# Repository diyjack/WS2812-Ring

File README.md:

# WS2812-Ring
Ring with 8/12/16/24/32/40/60 WS2812B intelligent RGB-LEDs.

## Shop
* [WS2812-Ring 8 (white)](http://www.watterott.com/en/WS2812B-RGB-Ring-8), [WS2812-Ring 8 (black)](http://www.watterott.com/en/WS2812-RGB-Ring-8-Black-Edition)
* [WS2812-Ring 12 (white)](http://www.watterott.com/en/WS2812B-RGB-Ring-12), [WS2812-Ring 12 (black)](http://www.watterott.com/en/WS2812-RGB-Ring-12-Black-Edition)
* [WS2812-Ring 16 (white)](http://www.watterott.com/en/WS2812B-RGB-Ring-16), [WS2812-Ring 16 (black)](http://www.watterott.com/en/WS2812-RGB-Ring-16-Black-Edition)
* [WS2812-Ring 24 (white)](http://www.watterott.com/en/WS2812B-RGB-Ring-24), [WS2812-Ring 24 (black)](http://www.watterott.com/en/WS2812-RGB-Ring-24-Black-Edition)
* [WS2812-Ring 32 (white)](http://www.watterott.com/en/WS2812B-RGB-Ring-32), [WS2812-Ring 32 (black)](http://www.watterott.com/en/WS2812-RGB-Ring-32-Black-Edition)
* [WS2812-Ring 40 (white)](http://www.watterott.com/en/WS2812B-RGB-Ring-40), [WS2812-Ring 40 (black)](http://www.watterott.com/en/WS2812-RGB-Ring-40-Black-Edition)
* [WS2812-Ring 60 (white)](http://www.watterott.com/en/WS2812B-RGB-Ring-60), [WS2812-Ring 60 (black)](http://www.watterott.com/en/WS2812-RGB-Ring-60-Black-Edition)
* [WS2812-Ring Set (white)](http://www.watterott.com/en/WS2812B-RGB-Ring-Set), [WS2812-Ring Set (black)](http://www.watterott.com/en/WS2812-RGB-Ring-Set-Black-Edition)

## Features
* WS2812 RGB-LED with built-in controller with serial interface
* 3 pin connection: VCC, GND, Data
* Controllable with Adafruit NeoPixel Library

## Hardware
* [Schematics + Layout](https://github.com/watterott/WS2812-Ring/tree/master/pcb)
* Datasheet: [WS2812B](https://github.com/watterott/WS2812-Breakout/raw/master/pcb/WS2812B.pdf)
* Note: for protection connect a >= 300 ohm resistor between the LED data input and controller output pin.

## Software
* [Light weight WS2811/WS2812 Library](https://github.com/cpldcpu/light_ws2812)
* [Adafruit NeoPixel Library](https://github.com/adafruit/Adafruit_NeoPixel)

## Videos
* [WS2812-Rings controlled by an Arduino](http://www.youtube.com/watch?v=nubyADJ7BFQ)
* [WS2812-Rings controlled by an Arduino](http://www.youtube.com/watch?v=e86KrhKNgWE)

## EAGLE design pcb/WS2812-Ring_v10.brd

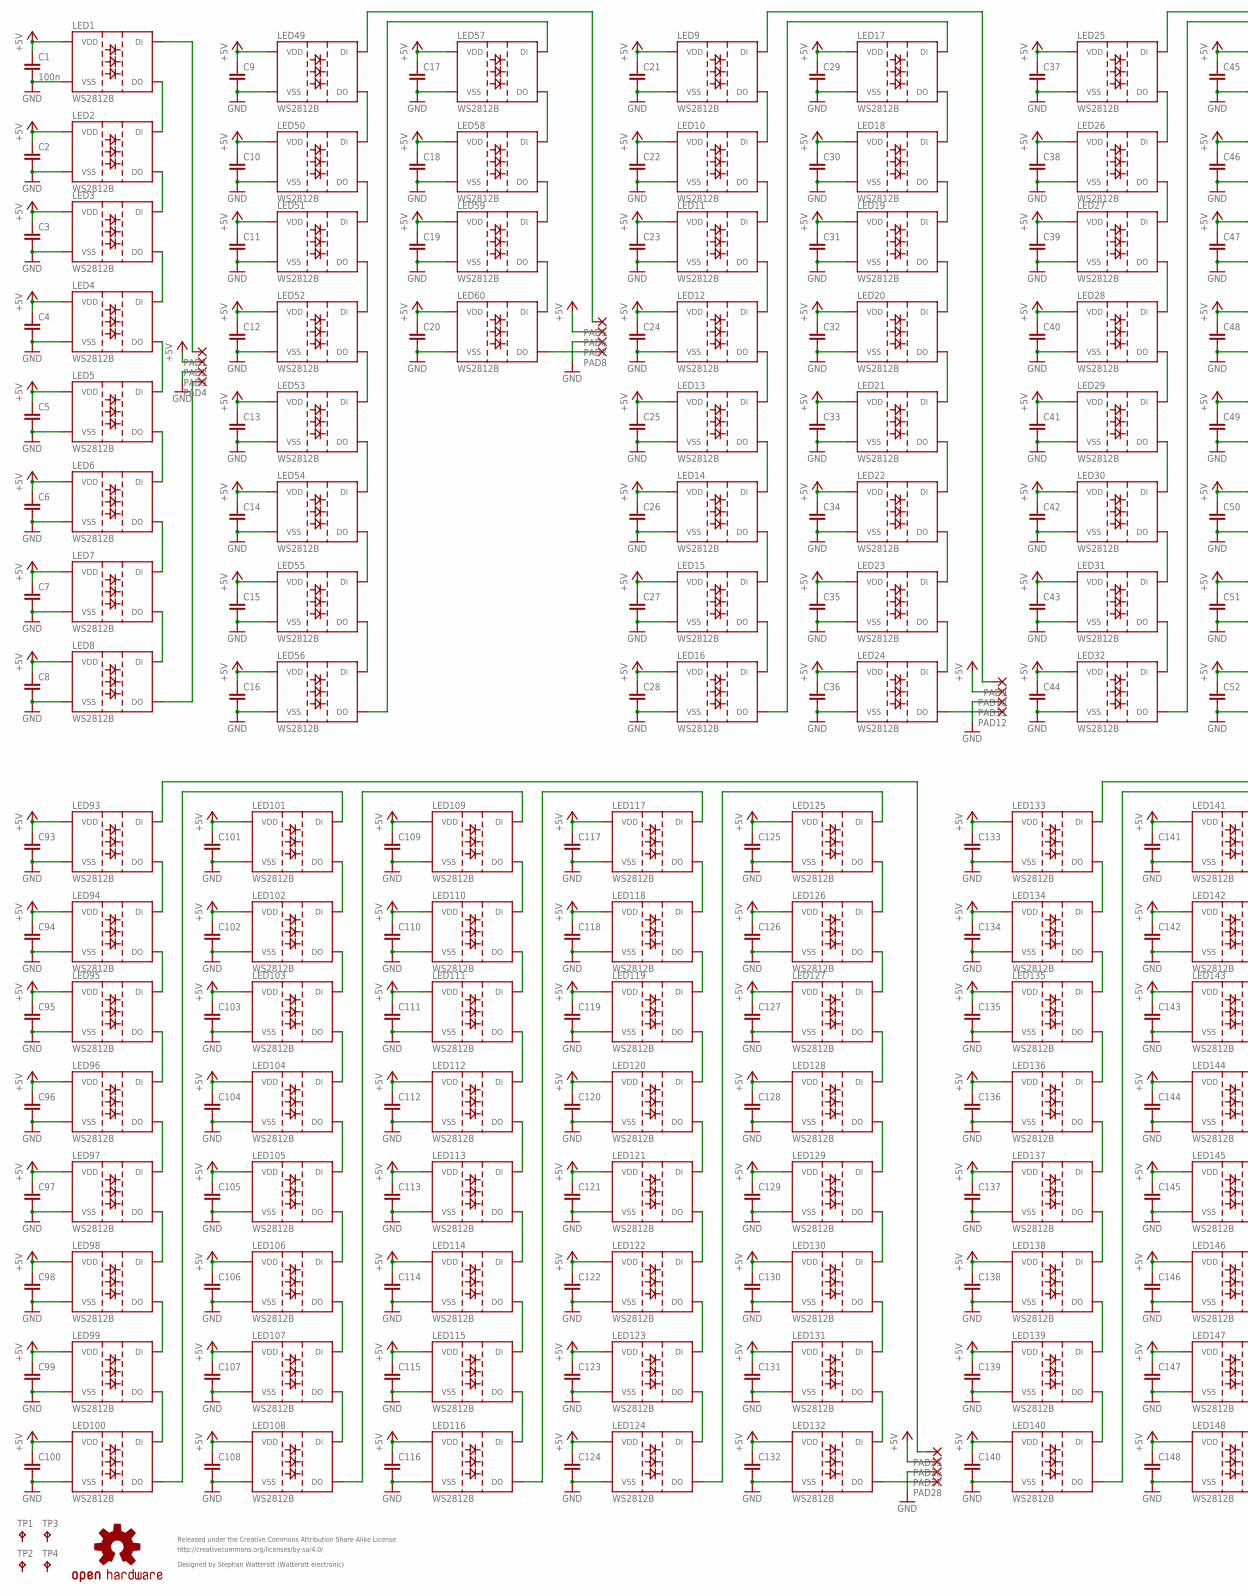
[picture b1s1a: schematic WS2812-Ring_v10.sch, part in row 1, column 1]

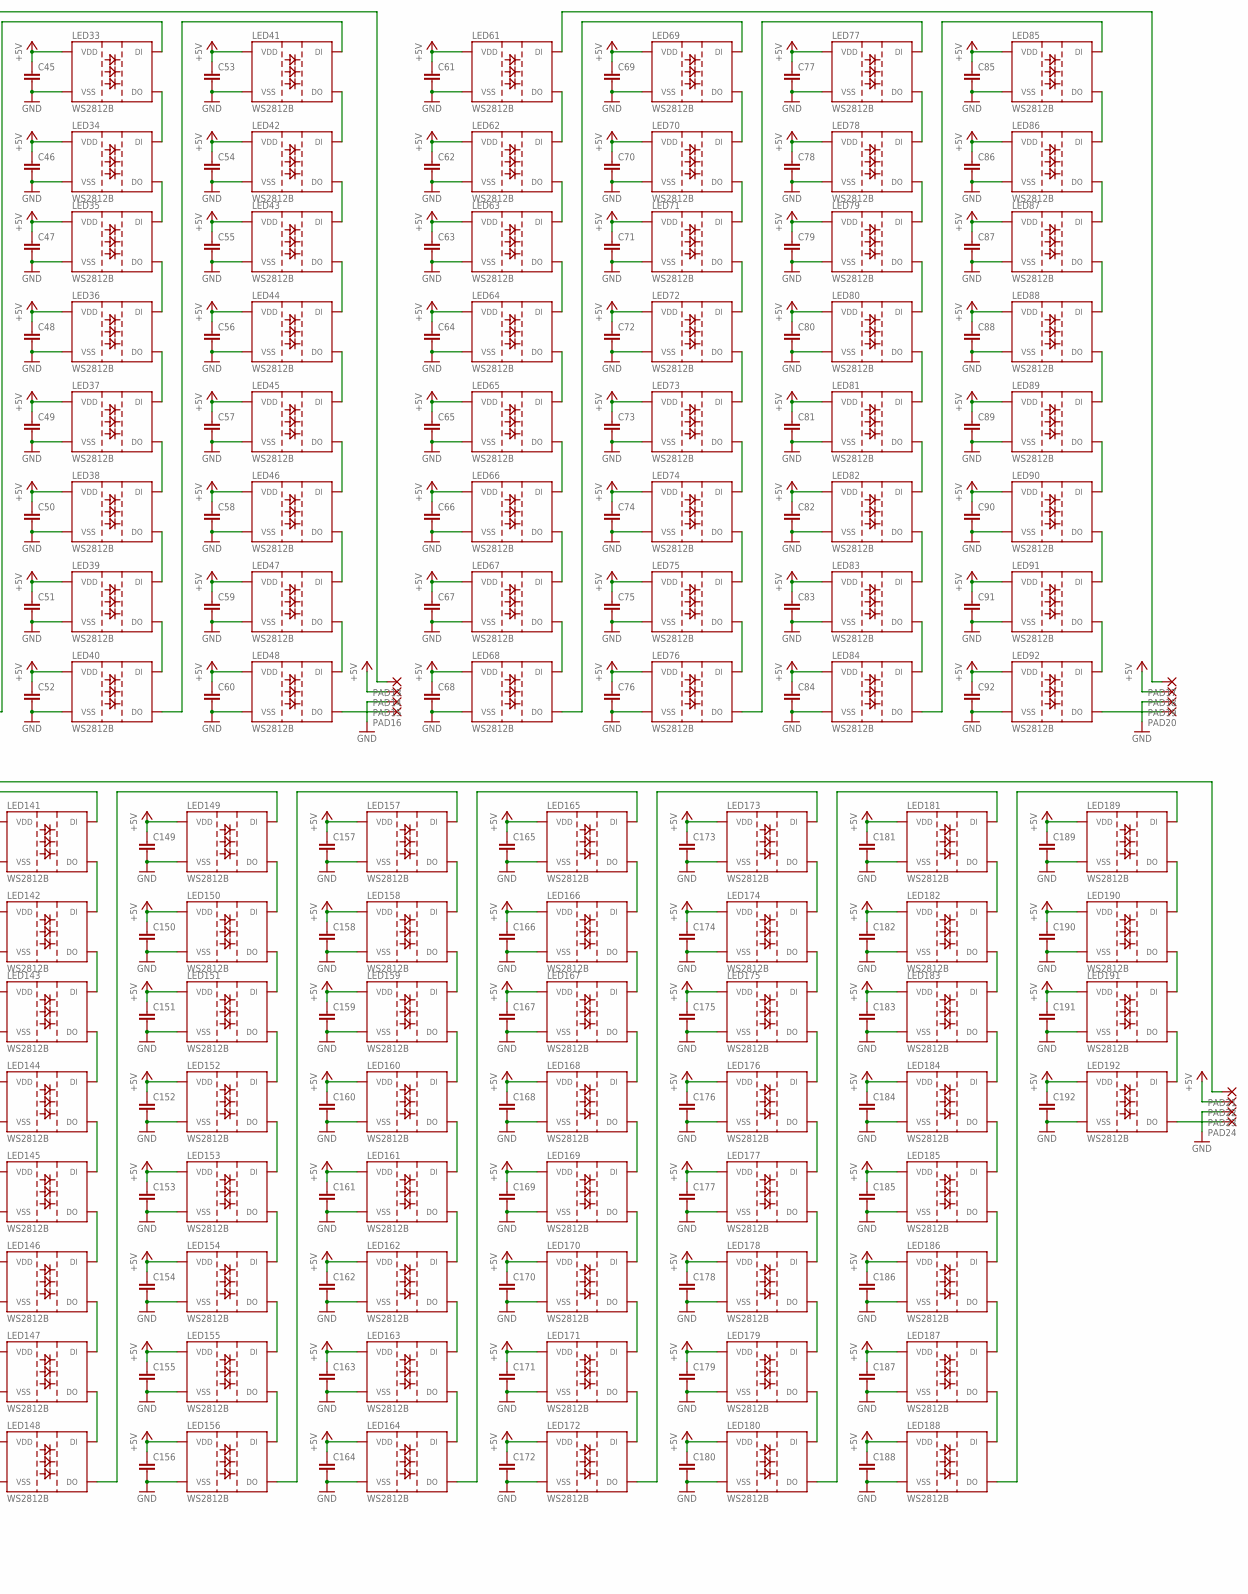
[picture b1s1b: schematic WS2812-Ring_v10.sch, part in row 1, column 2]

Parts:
C1: 100n; C0402K
C2, C3, C4, C5, C6, C7, C8, C9, C10, C11, C12, C13, C14, C15, C16, C17, C18, C19, C20, C21, C22, C23, C24, C25, C26, C27, C28, C29, C30, C31, C32, C33, C34, C35, C36, C37, C38, C39, C40, C41, C42, C43, C44, C45, C46, C47, C48, C49, C50, C51, C52, C53, C54, C55, C56, C57, C58, C59, C60, C61, C62, C63, C64, C65, C66, C67, C68, C69, C70, C71, C72, C73, C74, C75, C76, C77, C78, C79, C80, C81, C82, C83, C84, C85, C86, C87, C88, C89, C90, C91, C92, C93, C94, C95, C96, C97, C98, C99, C100, C101, C102, C103, C104, C105, C106, C107, C108, C109, C110, C111, C112, C113, C114, C115, C116, C117, C118, C119, C120, C121, C122, C123, C124, C125, C126, C127, C128, C129, C130, C131, C132, C133, C134, C135, C136, C137, C138, C139, C140, C141, C142, C143, C144, C145, C146, C147, C148, C149, C150, C151, C152, C153, C154, C155, C156, C157, C158, C159, C160, C161, C162, C163, C164, C165, C166, C167, C168, C169, C170, C171, C172, C173, C174, C175, C176, C177, C178, C179, C180, C181, C182, C183, C184, C185, C186, C187, C188, C189, C190, C191, C192: C-EUC0402K; C0402K
LED1, LED2, LED3, LED4, LED5, LED6, LED7, LED8, LED9, LED10, LED11, LED12, LED13, LED14, LED15, LED16, LED17, LED18, LED19, LED20, LED21, LED22, LED23, LED24, LED25, LED26, LED27, LED28, LED29, LED30, LED31, LED32, LED33, LED34, LED35, LED36, LED37, LED38, LED39, LED40, LED41, LED42, LED43, LED44, LED45, LED46, LED47, LED48, LED49, LED50, LED51, LED52, LED53, LED54, LED55, LED56, LED57, LED58, LED59, LED60, LED61, LED62, LED63, LED64, LED65, LED66, LED67, LED68, LED69, LED70, LED71, LED72, LED73, LED74, LED75, LED76, LED77, LED78, LED79, LED80, LED81, LED82, LED83, LED84, LED85, LED86, LED87, LED88, LED89, LED90, LED91, LED92, LED93, LED94, LED95, LED96, LED97, LED98, LED99, LED100, LED101, LED102, LED103, LED104, LED105, LED106, LED107, LED108, LED109, LED110, LED111, LED112, LED113, LED114, LED115, LED116, LED117, LED118, LED119, LED120, LED121, LED122, LED123, LED124, LED125, LED126, LED127, LED128, LED129, LED130, LED131, LED132, LED133, LED134, LED135, LED136, LED137, LED138, LED139, LED140, LED141, LED142, LED143, LED144, LED145, LED146, LED147, LED148, LED149, LED150, LED151, LED152, LED153, LED154, LED155, LED156, LED157, LED158, LED159, LED160, LED161, LED162, LED163, LED164, LED165, LED166, LED167, LED168, LED169, LED170, LED171, LED172, LED173, LED174, LED175, LED176, LED177, LED178, LED179, LED180, LED181, LED182, LED183, LED184, LED185, LED186, LED187, LED188, LED189, LED190, LED191, LED192: WS2812B
LOGO7: OSHW-LOGOM; OSHW-LOGO-M
PAD1, PAD2, PAD3, PAD4, PAD5, PAD6, PAD7, PAD8, PAD9, PAD10, PAD11, PAD12, PAD13, PAD14, PAD15, PAD16, PAD17, PAD18, PAD19, PAD20, PAD21, PAD22, PAD23, PAD24, PAD25, PAD26, PAD27, PAD28: SMD2; SMD1,27-2,54
TP1, TP2, TP3, TP4: TPB1,27; B1,27

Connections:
+5V: C1.1, C2.1, C3.1, C4.1, C5.1, C6.1, C7.1, C8.1, C9.1, C10.1, C11.1, C12.1, C13.1, C14.1, C15.1, C16.1, C17.1, C18.1, C19.1, C20.1, C21.1, C22.1, C23.1, C24.1, C25.1, C26.1, C27.1, C28.1, C29.1, C30.1, C31.1, C32.1, C33.1, C34.1, C35.1, C36.1, C37.1, C38.1, C39.1, C40.1, C41.1, C42.1, C43.1, C44.1, C45.1, C46.1, C47.1, C48.1, C49.1, C50.1, C51.1, C52.1, C53.1, C54.1, C55.1, C56.1, C57.1, C58.1, C59.1, C60.1, C61.1, C62.1, C63.1, C64.1, C65.1, C66.1, C67.1, C68.1, C69.1, C70.1, C71.1, C72.1, C73.1, C74.1, C75.1, C76.1, C77.1, C78.1, C79.1, C80.1, C81.1, C82.1, C83.1, C84.1, C85.1, C86.1, C87.1, C88.1, C89.1, C90.1, C91.1, C92.1, C93.1, C94.1, C95.1, C96.1, C97.1, C98.1, C99.1, C100.1, C101.1, C102.1, C103.1, C104.1, C105.1, C106.1, C107.1, C108.1, C109.1, C110.1, C111.1, C112.1, C113.1, C114.1, C115.1, C116.1, C117.1, C118.1, C119.1, C120.1, C121.1, C122.1, C123.1, C124.1, C125.1, C126.1, C127.1, C128.1, C129.1, C130.1, C131.1, C132.1, C133.1, C134.1, C135.1, C136.1, C137.1, C138.1, C139.1, C140.1, C141.1, C142.1, C143.1, C144.1, C145.1, C146.1, C147.1, C148.1, C149.1, C150.1, C151.1, C152.1, C153.1, C154.1, C155.1, C156.1, C157.1, C158.1, C159.1, C160.1, C161.1, C162.1, C163.1, C164.1, C165.1, C166.1, C167.1, C168.1, C169.1, C170.1, C171.1, C172.1, C173.1, C174.1, C175.1, C176.1, C177.1, C178.1, C179.1, C180.1, C181.1, C182.1, C183.1, C184.1, C185.1, C186.1, C187.1, C188.1, C189.1, C190.1, C191.1, C192.1, LED1.1 (VDD), LED2.1 (VDD), LED3.1 (VDD), LED4.1 (VDD), LED5.1 (VDD), LED6.1 (VDD), LED7.1 (VDD), LED8.1 (VDD), LED9.1 (VDD), LED10.1 (VDD), LED11.1 (VDD), LED12.1 (VDD), LED13.1 (VDD), LED14.1 (VDD), LED15.1 (VDD), LED16.1 (VDD), LED17.1 (VDD), LED18.1 (VDD), LED19.1 (VDD), LED20.1 (VDD), LED21.1 (VDD), LED22.1 (VDD), LED23.1 (VDD), LED24.1 (VDD), LED25.1 (VDD), LED26.1 (VDD), LED27.1 (VDD), LED28.1 (VDD), LED29.1 (VDD), LED30.1 (VDD), LED31.1 (VDD), LED32.1 (VDD), LED33.1 (VDD), LED34.1 (VDD), LED35.1 (VDD), LED36.1 (VDD), LED37.1 (VDD), LED38.1 (VDD), LED39.1 (VDD), LED40.1 (VDD), LED41.1 (VDD), LED42.1 (VDD), LED43.1 (VDD), LED44.1 (VDD), LED45.1 (VDD), LED46.1 (VDD), LED47.1 (VDD), LED48.1 (VDD), LED49.1 (VDD), LED50.1 (VDD), LED51.1 (VDD), LED52.1 (VDD), LED53.1 (VDD), LED54.1 (VDD), LED55.1 (VDD), LED56.1 (VDD), LED57.1 (VDD), LED58.1 (VDD), LED59.1 (VDD), LED60.1 (VDD), LED61.1 (VDD), LED62.1 (VDD), LED63.1 (VDD), LED64.1 (VDD), LED65.1 (VDD), LED66.1 (VDD), LED67.1 (VDD), LED68.1 (VDD), LED69.1 (VDD), LED70.1 (VDD), LED71.1 (VDD), LED72.1 (VDD), LED73.1 (VDD), LED74.1 (VDD), LED75.1 (VDD), LED76.1 (VDD), LED77.1 (VDD), LED78.1 (VDD), LED79.1 (VDD), LED80.1 (VDD), LED81.1 (VDD), LED82.1 (VDD), LED83.1 (VDD), LED84.1 (VDD), LED85.1 (VDD), LED86.1 (VDD), LED87.1 (VDD), LED88.1 (VDD), LED89.1 (VDD), LED90.1 (VDD), LED91.1 (VDD), LED92.1 (VDD), LED93.1 (VDD), LED94.1 (VDD), LED95.1 (VDD), LED96.1 (VDD), LED97.1 (VDD), LED98.1 (VDD), LED99.1 (VDD), LED100.1 (VDD), LED101.1 (VDD), LED102.1 (VDD), LED103.1 (VDD), LED104.1 (VDD), LED105.1 (VDD), LED106.1 (VDD), LED107.1 (VDD), LED108.1 (VDD), LED109.1 (VDD), LED110.1 (VDD), LED111.1 (VDD), LED112.1 (VDD), LED113.1 (VDD), LED114.1 (VDD), LED115.1 (VDD), LED116.1 (VDD), LED117.1 (VDD), LED118.1 (VDD), LED119.1 (VDD), LED120.1 (VDD), LED121.1 (VDD), LED122.1 (VDD), LED123.1 (VDD), LED124.1 (VDD), LED125.1 (VDD), LED126.1 (VDD), LED127.1 (VDD), LED128.1 (VDD), LED129.1 (VDD), LED130.1 (VDD), LED131.1 (VDD), LED132.1 (VDD), LED133.1 (VDD), LED134.1 (VDD), LED135.1 (VDD), LED136.1 (VDD), LED137.1 (VDD), LED138.1 (VDD), LED139.1 (VDD), LED140.1 (VDD), LED141.1 (VDD), LED142.1 (VDD), LED143.1 (VDD), LED144.1 (VDD), LED145.1 (VDD), LED146.1 (VDD), LED147.1 (VDD), LED148.1 (VDD), LED149.1 (VDD), LED150.1 (VDD), LED151.1 (VDD), LED152.1 (VDD), LED153.1 (VDD), LED154.1 (VDD), LED155.1 (VDD), LED156.1 (VDD), LED157.1 (VDD), LED158.1 (VDD), LED159.1 (VDD), LED160.1 (VDD), LED161.1 (VDD), LED162.1 (VDD), LED163.1 (VDD), LED164.1 (VDD), LED165.1 (VDD), LED166.1 (VDD), LED167.1 (VDD), LED168.1 (VDD), LED169.1 (VDD), LED170.1 (VDD), LED171.1 (VDD), LED172.1 (VDD), LED173.1 (VDD), LED174.1 (VDD), LED175.1 (VDD), LED176.1 (VDD), LED177.1 (VDD), LED178.1 (VDD), LED179.1 (VDD), LED180.1 (VDD), LED181.1 (VDD), LED182.1 (VDD), LED183.1 (VDD), LED184.1 (VDD), LED185.1 (VDD), LED186.1 (VDD), LED187.1 (VDD), LED188.1 (VDD), LED189.1 (VDD), LED190.1 (VDD), LED191.1 (VDD), LED192.1 (VDD), PAD2.1, PAD6.1, PAD10.1, PAD14.1, PAD18.1, PAD22.1, PAD26.1
GND: C1.2, C2.2, C3.2, C4.2, C5.2, C6.2, C7.2, C8.2, C9.2, C10.2, C11.2, C12.2, C13.2, C14.2, C15.2, C16.2, C17.2, C18.2, C19.2, C20.2, C21.2, C22.2, C23.2, C24.2, C25.2, C26.2, C27.2, C28.2, C29.2, C30.2, C31.2, C32.2, C33.2, C34.2, C35.2, C36.2, C37.2, C38.2, C39.2, C40.2, C41.2, C42.2, C43.2, C44.2, C45.2, C46.2, C47.2, C48.2, C49.2, C50.2, C51.2, C52.2, C53.2, C54.2, C55.2, C56.2, C57.2, C58.2, C59.2, C60.2, C61.2, C62.2, C63.2, C64.2, C65.2, C66.2, C67.2, C68.2, C69.2, C70.2, C71.2, C72.2, C73.2, C74.2, C75.2, C76.2, C77.2, C78.2, C79.2, C80.2, C81.2, C82.2, C83.2, C84.2, C85.2, C86.2, C87.2, C88.2, C89.2, C90.2, C91.2, C92.2, C93.2, C94.2, C95.2, C96.2, C97.2, C98.2, C99.2, C100.2, C101.2, C102.2, C103.2, C104.2, C105.2, C106.2, C107.2, C108.2, C109.2, C110.2, C111.2, C112.2, C113.2, C114.2, C115.2, C116.2, C117.2, C118.2, C119.2, C120.2, C121.2, C122.2, C123.2, C124.2, C125.2, C126.2, C127.2, C128.2, C129.2, C130.2, C131.2, C132.2, C133.2, C134.2, C135.2, C136.2, C137.2, C138.2, C139.2, C140.2, C141.2, C142.2, C143.2, C144.2, C145.2, C146.2, C147.2, C148.2, C149.2, C150.2, C151.2, C152.2, C153.2, C154.2, C155.2, C156.2, C157.2, C158.2, C159.2, C160.2, C161.2, C162.2, C163.2, C164.2, C165.2, C166.2, C167.2, C168.2, C169.2, C170.2, C171.2, C172.2, C173.2, C174.2, C175.2, C176.2, C177.2, C178.2, C179.2, C180.2, C181.2, C182.2, C183.2, C184.2, C185.2, C186.2, C187.2, C188.2, C189.2, C190.2, C191.2, C192.2, LED1.3 (VSS), LED2.3 (VSS), LED3.3 (VSS), LED4.3 (VSS), LED5.3 (VSS), LED6.3 (VSS), LED7.3 (VSS), LED8.3 (VSS), LED9.3 (VSS), LED10.3 (VSS), LED11.3 (VSS), LED12.3 (VSS), LED13.3 (VSS), LED14.3 (VSS), LED15.3 (VSS), LED16.3 (VSS), LED17.3 (VSS), LED18.3 (VSS), LED19.3 (VSS), LED20.3 (VSS), LED21.3 (VSS), LED22.3 (VSS), LED23.3 (VSS), LED24.3 (VSS), LED25.3 (VSS), LED26.3 (VSS), LED27.3 (VSS), LED28.3 (VSS), LED29.3 (VSS), LED30.3 (VSS), LED31.3 (VSS), LED32.3 (VSS), LED33.3 (VSS), LED34.3 (VSS), LED35.3 (VSS), LED36.3 (VSS), LED37.3 (VSS), LED38.3 (VSS), LED39.3 (VSS), LED40.3 (VSS), LED41.3 (VSS), LED42.3 (VSS), LED43.3 (VSS), LED44.3 (VSS), LED45.3 (VSS), LED46.3 (VSS), LED47.3 (VSS), LED48.3 (VSS), LED49.3 (VSS), LED50.3 (VSS), LED51.3 (VSS), LED52.3 (VSS), LED53.3 (VSS), LED54.3 (VSS), LED55.3 (VSS), LED56.3 (VSS), LED57.3 (VSS), LED58.3 (VSS), LED59.3 (VSS), LED60.3 (VSS), LED61.3 (VSS), LED62.3 (VSS), LED63.3 (VSS), LED64.3 (VSS), LED65.3 (VSS), LED66.3 (VSS), LED67.3 (VSS), LED68.3 (VSS), LED69.3 (VSS), LED70.3 (VSS), LED71.3 (VSS), LED72.3 (VSS), LED73.3 (VSS), LED74.3 (VSS), LED75.3 (VSS), LED76.3 (VSS), LED77.3 (VSS), LED78.3 (VSS), LED79.3 (VSS), LED80.3 (VSS), LED81.3 (VSS), LED82.3 (VSS), LED83.3 (VSS), LED84.3 (VSS), LED85.3 (VSS), LED86.3 (VSS), LED87.3 (VSS), LED88.3 (VSS), LED89.3 (VSS), LED90.3 (VSS), LED91.3 (VSS), LED92.3 (VSS), LED93.3 (VSS), LED94.3 (VSS), LED95.3 (VSS), LED96.3 (VSS), LED97.3 (VSS), LED98.3 (VSS), LED99.3 (VSS), LED100.3 (VSS), LED101.3 (VSS), LED102.3 (VSS), LED103.3 (VSS), LED104.3 (VSS), LED105.3 (VSS), LED106.3 (VSS), LED107.3 (VSS), LED108.3 (VSS), LED109.3 (VSS), LED110.3 (VSS), LED111.3 (VSS), LED112.3 (VSS), LED113.3 (VSS), LED114.3 (VSS), LED115.3 (VSS), LED116.3 (VSS), LED117.3 (VSS), LED118.3 (VSS), LED119.3 (VSS), LED120.3 (VSS), LED121.3 (VSS), LED122.3 (VSS), LED123.3 (VSS), LED124.3 (VSS), LED125.3 (VSS), LED126.3 (VSS), LED127.3 (VSS), LED128.3 (VSS), LED129.3 (VSS), LED130.3 (VSS), LED131.3 (VSS), LED132.3 (VSS), LED133.3 (VSS), LED134.3 (VSS), LED135.3 (VSS), LED136.3 (VSS), LED137.3 (VSS), LED138.3 (VSS), LED139.3 (VSS), LED140.3 (VSS), LED141.3 (VSS), LED142.3 (VSS), LED143.3 (VSS), LED144.3 (VSS), LED145.3 (VSS), LED146.3 (VSS), LED147.3 (VSS), LED148.3 (VSS), LED149.3 (VSS), LED150.3 (VSS), LED151.3 (VSS), LED152.3 (VSS), LED153.3 (VSS), LED154.3 (VSS), LED155.3 (VSS), LED156.3 (VSS), LED157.3 (VSS), LED158.3 (VSS), LED159.3 (VSS), LED160.3 (VSS), LED161.3 (VSS), LED162.3 (VSS), LED163.3 (VSS), LED164.3 (VSS), LED165.3 (VSS), LED166.3 (VSS), LED167.3 (VSS), LED168.3 (VSS), LED169.3 (VSS), LED170.3 (VSS), LED171.3 (VSS), LED172.3 (VSS), LED173.3 (VSS), LED174.3 (VSS), LED175.3 (VSS), LED176.3 (VSS), LED177.3 (VSS), LED178.3 (VSS), LED179.3 (VSS), LED180.3 (VSS), LED181.3 (VSS), LED182.3 (VSS), LED183.3 (VSS), LED184.3 (VSS), LED185.3 (VSS), LED186.3 (VSS), LED187.3 (VSS), LED188.3 (VSS), LED189.3 (VSS), LED190.3 (VSS), LED191.3 (VSS), LED192.3 (VSS), PAD3.1, PAD7.1, PAD11.1, PAD15.1, PAD19.1, PAD23.1, PAD27.1
unnamed: LED1.2 (DO), LED2.4 (DI)
unnamed: LED2.2 (DO), LED3.4 (DI)
unnamed: LED3.2 (DO), LED4.4 (DI)
unnamed: LED4.2 (DO), LED5.4 (DI)
unnamed: LED5.2 (DO), LED6.4 (DI)
unnamed: LED6.2 (DO), LED7.4 (DI)
unnamed: LED7.2 (DO), LED8.4 (DI)
unnamed: LED9.2 (DO), LED10.4 (DI)
unnamed: LED10.2 (DO), LED11.4 (DI)
unnamed: LED11.2 (DO), LED12.4 (DI)
unnamed: LED12.2 (DO), LED13.4 (DI)
unnamed: LED13.2 (DO), LED14.4 (DI)
unnamed: LED14.2 (DO), LED15.4 (DI)
unnamed: LED15.2 (DO), LED16.4 (DI)
unnamed: LED17.2 (DO), LED18.4 (DI)
unnamed: LED18.2 (DO), LED19.4 (DI)
unnamed: LED19.2 (DO), LED20.4 (DI)
unnamed: LED20.2 (DO), LED21.4 (DI)
unnamed: LED21.2 (DO), LED22.4 (DI)
unnamed: LED22.2 (DO), LED23.4 (DI)
unnamed: LED23.2 (DO), LED24.4 (DI)
unnamed: LED16.2 (DO), LED17.4 (DI)
unnamed: LED25.2 (DO), LED26.4 (DI)
unnamed: LED26.2 (DO), LED27.4 (DI)
unnamed: LED27.2 (DO), LED28.4 (DI)
unnamed: LED28.2 (DO), LED29.4 (DI)
unnamed: LED29.2 (DO), LED30.4 (DI)
unnamed: LED30.2 (DO), LED31.4 (DI)
unnamed: LED31.2 (DO), LED32.4 (DI)
unnamed: LED33.2 (DO), LED34.4 (DI)
unnamed: LED34.2 (DO), LED35.4 (DI)
unnamed: LED35.2 (DO), LED36.4 (DI)
unnamed: LED36.2 (DO), LED37.4 (DI)
unnamed: LED37.2 (DO), LED38.4 (DI)
unnamed: LED38.2 (DO), LED39.4 (DI)
unnamed: LED39.2 (DO), LED40.4 (DI)
unnamed: LED32.2 (DO), LED33.4 (DI)
unnamed: LED41.2 (DO), LED42.4 (DI)
unnamed: LED42.2 (DO), LED43.4 (DI)
unnamed: LED43.2 (DO), LED44.4 (DI)
unnamed: LED44.2 (DO), LED45.4 (DI)
unnamed: LED45.2 (DO), LED46.4 (DI)
unnamed: LED46.2 (DO), LED47.4 (DI)
unnamed: LED47.2 (DO), LED48.4 (DI)
unnamed: LED40.2 (DO), LED41.4 (DI)
unnamed: LED49.2 (DO), LED50.4 (DI)
unnamed: LED50.2 (DO), LED51.4 (DI)
unnamed: LED51.2 (DO), LED52.4 (DI)
unnamed: LED52.2 (DO), LED53.4 (DI)
unnamed: LED53.2 (DO), LED54.4 (DI)
unnamed: LED54.2 (DO), LED55.4 (DI)
unnamed: LED55.2 (DO), LED56.4 (DI)
unnamed: LED57.2 (DO), LED58.4 (DI)
unnamed: LED58.2 (DO), LED59.4 (DI)
unnamed: LED59.2 (DO), LED60.4 (DI)
unnamed: LED1.4 (DI), PAD1.1
unnamed: LED56.2 (DO), LED57.4 (DI)
unnamed: LED61.2 (DO), LED62.4 (DI)
unnamed: LED62.2 (DO), LED63.4 (DI)
unnamed: LED63.2 (DO), LED64.4 (DI)
unnamed: LED64.2 (DO), LED65.4 (DI)
unnamed: LED65.2 (DO), LED66.4 (DI)
unnamed: LED66.2 (DO), LED67.4 (DI)
unnamed: LED67.2 (DO), LED68.4 (DI)
unnamed: LED69.2 (DO), LED70.4 (DI)
unnamed: LED70.2 (DO), LED71.4 (DI)
unnamed: LED71.2 (DO), LED72.4 (DI)
unnamed: LED72.2 (DO), LED73.4 (DI)
unnamed: LED73.2 (DO), LED74.4 (DI)
unnamed: LED74.2 (DO), LED75.4 (DI)
unnamed: LED75.2 (DO), LED76.4 (DI)
unnamed: LED68.2 (DO), LED69.4 (DI)
unnamed: LED77.2 (DO), LED78.4 (DI)
unnamed: LED78.2 (DO), LED79.4 (DI)
unnamed: LED79.2 (DO), LED80.4 (DI)
unnamed: LED80.2 (DO), LED81.4 (DI)
unnamed: LED81.2 (DO), LED82.4 (DI)
unnamed: LED82.2 (DO), LED83.4 (DI)
unnamed: LED83.2 (DO), LED84.4 (DI)
unnamed: LED76.2 (DO), LED77.4 (DI)
unnamed: LED85.2 (DO), LED86.4 (DI)
unnamed: LED86.2 (DO), LED87.4 (DI)
unnamed: LED87.2 (DO), LED88.4 (DI)
unnamed: LED88.2 (DO), LED89.4 (DI)
unnamed: LED89.2 (DO), LED90.4 (DI)
unnamed: LED90.2 (DO), LED91.4 (DI)
unnamed: LED91.2 (DO), LED92.4 (DI)
unnamed: LED84.2 (DO), LED85.4 (DI)
unnamed: LED93.2 (DO), LED94.4 (DI)
unnamed: LED94.2 (DO), LED95.4 (DI)
unnamed: LED95.2 (DO), LED96.4 (DI)
unnamed: LED96.2 (DO), LED97.4 (DI)
unnamed: LED97.2 (DO), LED98.4 (DI)
unnamed: LED98.2 (DO), LED99.4 (DI)
unnamed: LED99.2 (DO), LED100.4 (DI)
unnamed: LED101.2 (DO), LED102.4 (DI)
unnamed: LED102.2 (DO), LED103.4 (DI)
unnamed: LED103.2 (DO), LED104.4 (DI)
unnamed: LED104.2 (DO), LED105.4 (DI)
unnamed: LED105.2 (DO), LED106.4 (DI)
unnamed: LED106.2 (DO), LED107.4 (DI)
unnamed: LED107.2 (DO), LED108.4 (DI)
unnamed: LED100.2 (DO), LED101.4 (DI)
unnamed: LED109.2 (DO), LED110.4 (DI)
unnamed: LED110.2 (DO), LED111.4 (DI)
unnamed: LED111.2 (DO), LED112.4 (DI)
unnamed: LED112.2 (DO), LED113.4 (DI)
unnamed: LED113.2 (DO), LED114.4 (DI)
unnamed: LED114.2 (DO), LED115.4 (DI)
unnamed: LED115.2 (DO), LED116.4 (DI)
unnamed: LED108.2 (DO), LED109.4 (DI)
unnamed: LED117.2 (DO), LED118.4 (DI)
unnamed: LED118.2 (DO), LED119.4 (DI)
unnamed: LED119.2 (DO), LED120.4 (DI)
unnamed: LED120.2 (DO), LED121.4 (DI)
unnamed: LED121.2 (DO), LED122.4 (DI)
unnamed: LED122.2 (DO), LED123.4 (DI)
unnamed: LED123.2 (DO), LED124.4 (DI)
unnamed: LED116.2 (DO), LED117.4 (DI)
unnamed: LED125.2 (DO), LED126.4 (DI)
unnamed: LED126.2 (DO), LED127.4 (DI)
unnamed: LED127.2 (DO), LED128.4 (DI)
unnamed: LED128.2 (DO), LED129.4 (DI)
unnamed: LED129.2 (DO), LED130.4 (DI)
unnamed: LED130.2 (DO), LED131.4 (DI)
unnamed: LED131.2 (DO), LED132.4 (DI)
unnamed: LED124.2 (DO), LED125.4 (DI)
unnamed: LED133.2 (DO), LED134.4 (DI)
unnamed: LED134.2 (DO), LED135.4 (DI)
unnamed: LED135.2 (DO), LED136.4 (DI)
unnamed: LED136.2 (DO), LED137.4 (DI)
unnamed: LED137.2 (DO), LED138.4 (DI)
unnamed: LED138.2 (DO), LED139.4 (DI)
unnamed: LED139.2 (DO), LED140.4 (DI)
unnamed: LED141.2 (DO), LED142.4 (DI)
unnamed: LED142.2 (DO), LED143.4 (DI)
unnamed: LED143.2 (DO), LED144.4 (DI)
unnamed: LED144.2 (DO), LED145.4 (DI)
unnamed: LED145.2 (DO), LED146.4 (DI)
unnamed: LED146.2 (DO), LED147.4 (DI)
unnamed: LED147.2 (DO), LED148.4 (DI)
unnamed: LED140.2 (DO), LED141.4 (DI)
unnamed: LED149.2 (DO), LED150.4 (DI)
unnamed: LED150.2 (DO), LED151.4 (DI)
unnamed: LED151.2 (DO), LED152.4 (DI)
unnamed: LED152.2 (DO), LED153.4 (DI)
unnamed: LED153.2 (DO), LED154.4 (DI)
unnamed: LED154.2 (DO), LED155.4 (DI)
unnamed: LED155.2 (DO), LED156.4 (DI)
unnamed: LED148.2 (DO), LED149.4 (DI)
unnamed: LED157.2 (DO), LED158.4 (DI)
unnamed: LED158.2 (DO), LED159.4 (DI)
unnamed: LED159.2 (DO), LED160.4 (DI)
unnamed: LED160.2 (DO), LED161.4 (DI)
unnamed: LED161.2 (DO), LED162.4 (DI)
unnamed: LED162.2 (DO), LED163.4 (DI)
unnamed: LED163.2 (DO), LED164.4 (DI)
unnamed: LED156.2 (DO), LED157.4 (DI)
unnamed: LED165.2 (DO), LED166.4 (DI)
unnamed: LED166.2 (DO), LED167.4 (DI)
unnamed: LED167.2 (DO), LED168.4 (DI)
unnamed: LED168.2 (DO), LED169.4 (DI)
unnamed: LED169.2 (DO), LED170.4 (DI)
unnamed: LED170.2 (DO), LED171.4 (DI)
unnamed: LED171.2 (DO), LED172.4 (DI)
unnamed: LED164.2 (DO), LED165.4 (DI)
unnamed: LED173.2 (DO), LED174.4 (DI)
unnamed: LED174.2 (DO), LED175.4 (DI)
unnamed: LED175.2 (DO), LED176.4 (DI)
unnamed: LED176.2 (DO), LED177.4 (DI)
unnamed: LED177.2 (DO), LED178.4 (DI)
unnamed: LED178.2 (DO), LED179.4 (DI)
unnamed: LED179.2 (DO), LED180.4 (DI)
unnamed: LED172.2 (DO), LED173.4 (DI)
unnamed: LED181.2 (DO), LED182.4 (DI)
unnamed: LED182.2 (DO), LED183.4 (DI)
unnamed: LED183.2 (DO), LED184.4 (DI)
unnamed: LED184.2 (DO), LED185.4 (DI)
unnamed: LED185.2 (DO), LED186.4 (DI)
unnamed: LED186.2 (DO), LED187.4 (DI)
unnamed: LED187.2 (DO), LED188.4 (DI)
unnamed: LED180.2 (DO), LED181.4 (DI)
unnamed: LED189.2 (DO), LED190.4 (DI)
unnamed: LED190.2 (DO), LED191.4 (DI)
unnamed: LED191.2 (DO), LED192.4 (DI)
unnamed: LED8.2 (DO), PAD4.1
unnamed: LED49.4 (DI), PAD5.1
unnamed: LED60.2 (DO), PAD8.1
unnamed: LED24.2 (DO), PAD12.1
unnamed: LED188.2 (DO), LED189.4 (DI)
unnamed: LED48.2 (DO), PAD16.1
unnamed: LED92.2 (DO), PAD20.1
unnamed: LED192.2 (DO), PAD24.1
unnamed: LED132.2 (DO), PAD28.1
unnamed: LED9.4 (DI), PAD9.1
unnamed: LED25.4 (DI), PAD13.1
unnamed: LED61.4 (DI), PAD17.1
unnamed: LED133.4 (DI), PAD21.1
unnamed: LED93.4 (DI), PAD25.1

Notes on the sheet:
Released under the Creative Commons Attribution Share-Alike License
http://creativecommons.org/licenses/by-sa/4.0/
Designed by Stephan Watterott (Watterott electronic)

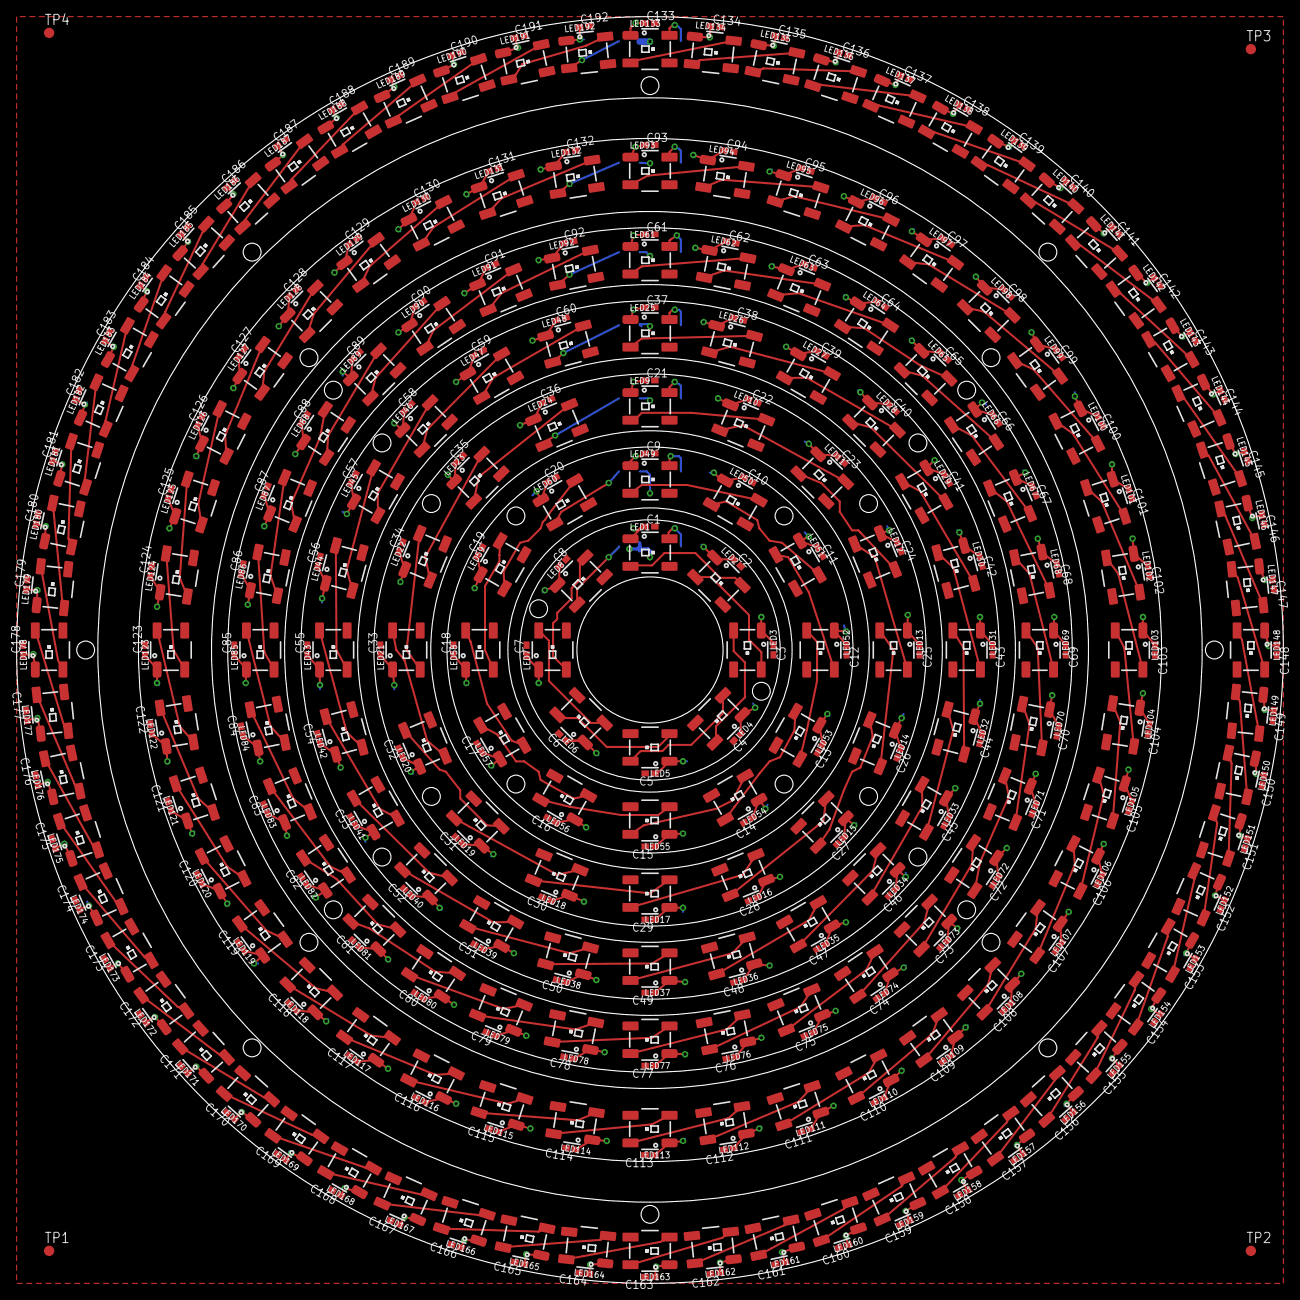
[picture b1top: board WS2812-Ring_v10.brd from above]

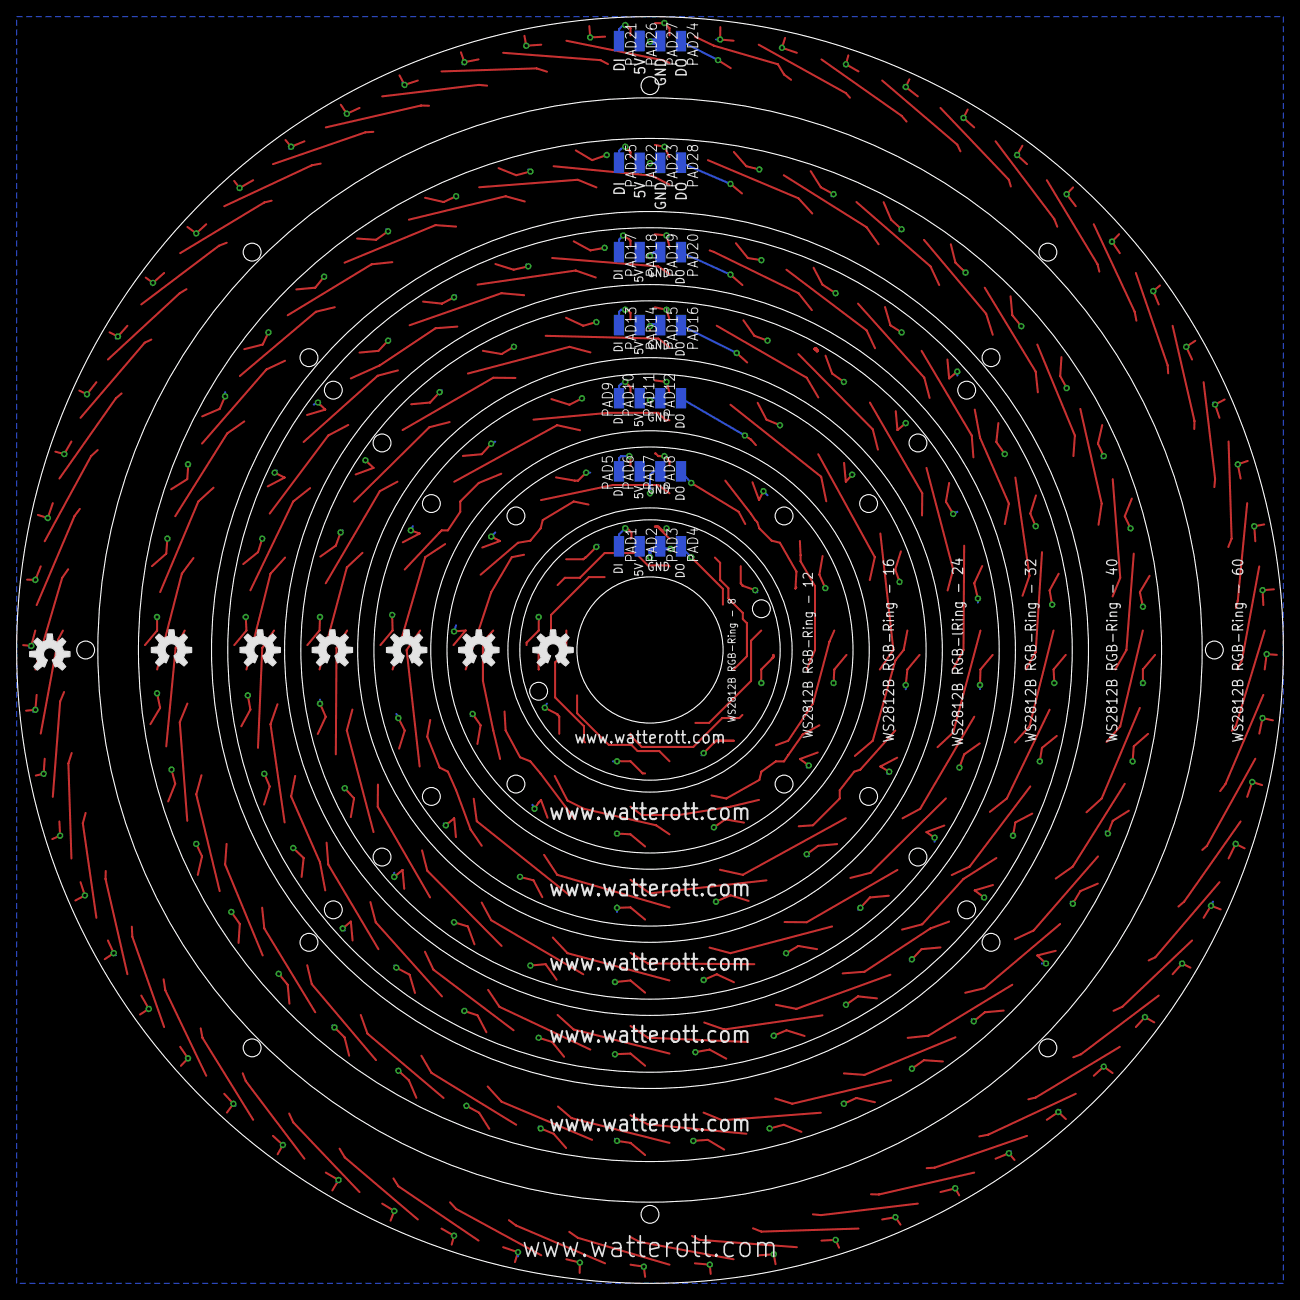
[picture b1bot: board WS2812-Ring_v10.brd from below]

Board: 2 copper layers, 156.0 x 156.0 mm, 423 parts (35 on the bottom side), 201 nets.

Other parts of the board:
LOGO1, LOGO2, LOGO3, LOGO4, LOGO5, LOGO6: OSHW-LOGOM; OSHW-LOGO-M

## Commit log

2014-03-11 added image
2014-03-11 added schematics and layout files
2014-06-11 renamed files
2014-06-28 updated datasheet
2014-08-21 updated layout and schematics
2014-11-06 cleaned up schematics and layout
2015-01-11 moved image

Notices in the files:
parts and their libraries:
SparkFun-Aesthetics: Licensing: CC v3.0 Share-Alike You are welcome to use this library for commercial purposes.
